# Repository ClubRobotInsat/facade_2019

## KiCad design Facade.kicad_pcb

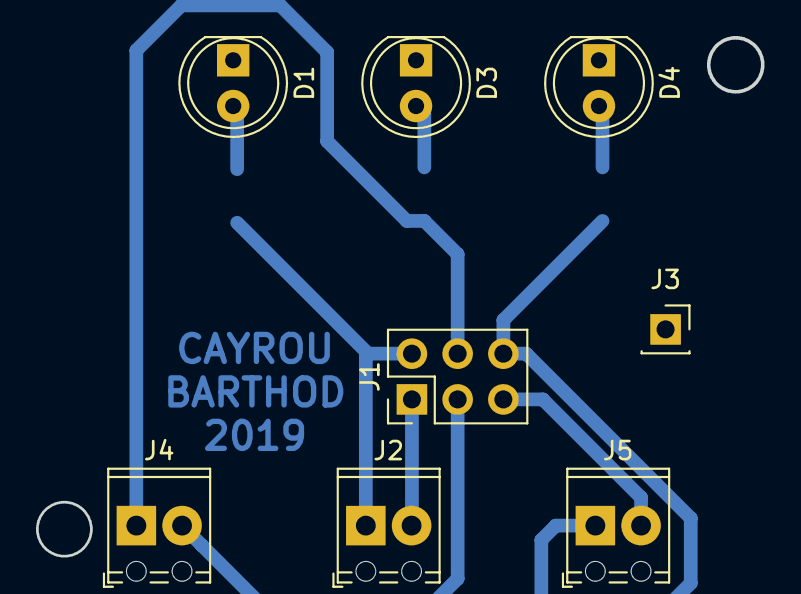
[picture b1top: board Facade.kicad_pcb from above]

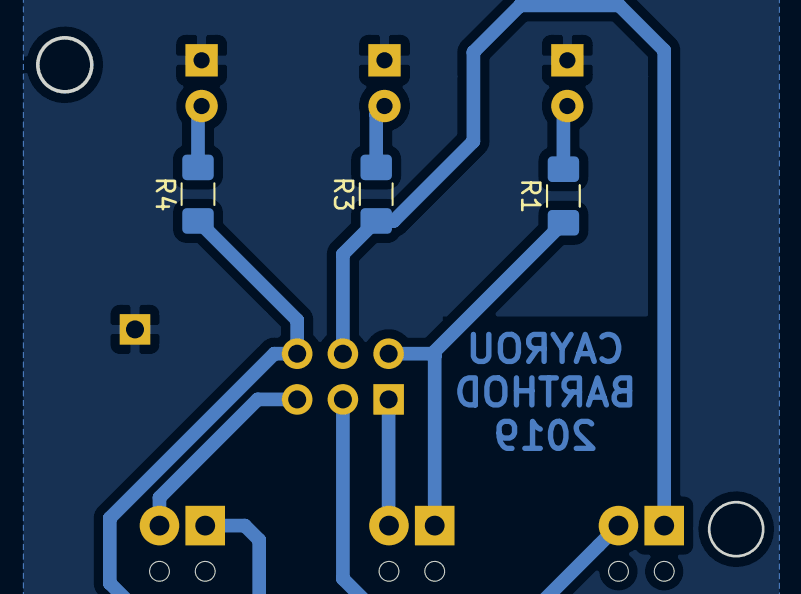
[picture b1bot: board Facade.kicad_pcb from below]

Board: 2 copper layers, 40.3 x 28.8 mm, 11 parts (3 on the bottom side), 10 nets.

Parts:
D1, D3, D4: LED; LED_D5.0mm
J1: Conn_02x03_Odd_Even; PinHeader_2x03_P2.54mm_Vertical
J2, J4, J5: Conn_01x02; TerminalBlock_Phoenix_MPT-0,5-2-2.54_1x02_P2.54mm_Horizontal
J3: Conn_01x01; PinSocket_1x01_P2.54mm_Vertical
R1, R3, R4: R; R_1206_3216Metric_Pad1.42x1.75mm_HandSolder

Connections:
+5V: J1.1, J2.2
+7.5V: J1.3, J4.2
+15V: J1.5, J5.2
GND: D1.1, D3.1, D4.1, J3.1
unnamed: D1.2, R1.2
unnamed: D3.2, R3.2
unnamed: D4.2, R4.2
unnamed: J1.2, J2.1, R1.1
unnamed: J1.4, J4.1, R3.1
unnamed: J1.6, J5.1, R4.1

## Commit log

2019-05-16 ajout version 1 carte facade mini robot
2019-05-16 v2 : ajout connetcteur plan de masse
2019-05-16 Use new connector
